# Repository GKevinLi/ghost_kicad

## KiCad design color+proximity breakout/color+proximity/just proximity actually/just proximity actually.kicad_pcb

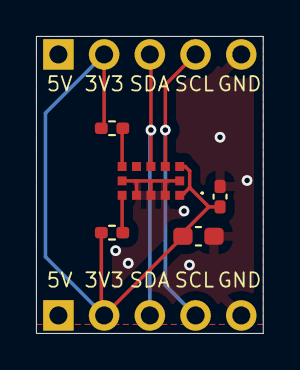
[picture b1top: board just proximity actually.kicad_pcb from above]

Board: 2 copper layers, 12.6 x 16.5 mm, 7 parts (0 on the bottom side), 7 nets.

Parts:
C11: 0.1u; C_0402_1005Metric_Pad0.74x0.62mm_HandSolder
C12: 4.7u; C_0603_1608Metric_Pad1.08x0.95mm_HandSolder
IC1: VL53L4CDV0DH_1; VL53L4CDV0DH1
J4, J4#2: Conn_01x05; PinHeader_1x05_P2.54mm_Vertical
R20, R21: 10k; R_0402_1005Metric_Pad0.72x0.64mm_HandSolder

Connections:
+3.3V: C11.1, C12.1, IC1.1 (AVDDVCSEL_1), IC1.11 (AVDD), IC1.13 (AVDDVCSEL_2), J4.2, J4#2.2, R20.2, R21.1
+5V: J4.1, J4#2.1
/scl: IC1.10 (SCL), J4.4, J4#2.4
/sda: IC1.9 (SDA), J4.3, J4#2.3
GND: C11.2, C12.2, IC1.2 (AVSSVCSEL), IC1.3 (GND), IC1.4 (GND2), IC1.6 (GND3), IC1.12 (GND4), J4.5, J4#2.5
unnamed: IC1.7 (GPIO1), R20.1
unnamed: IC1.5 (XSHUT), R21.2

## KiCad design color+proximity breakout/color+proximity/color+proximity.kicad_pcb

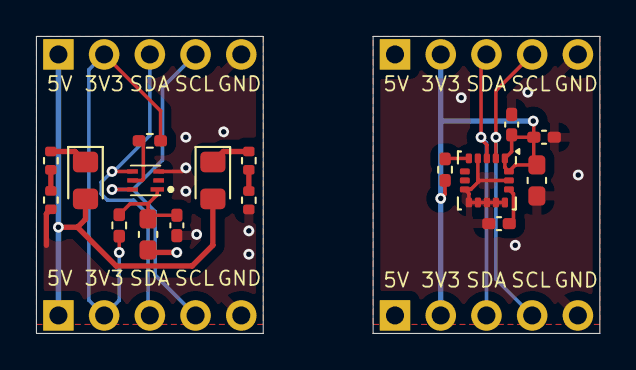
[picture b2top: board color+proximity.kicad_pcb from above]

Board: 2 copper layers, 31.3 x 16.5 mm, 21 parts (0 on the bottom side), 13 nets.

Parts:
C4: 1u; C_0603_1608Metric_Pad1.08x0.95mm_HandSolder
C5, C7, C10: 0.1u; C_0402_1005Metric_Pad0.74x0.62mm_HandSolder
C8: 2.2u; C_0603_1608Metric_Pad1.08x0.95mm_HandSolder
C9: 10n; C_0402_1005Metric_Pad0.74x0.62mm_HandSolder
D1, D2: WHITE; LED_0805_2012Metric_Pad1.15x1.40mm_HandSolder
IC2: ISL29125IROZ-T7; ISL29125IROZT7
J4, J4#2, J4#3, J4#4: Conn_01x05; PinHeader_1x05_P2.54mm_Vertical
R15: 100; R_0402_1005Metric_Pad0.72x0.64mm_HandSolder
R16, R19: 4.7k; R_0402_1005Metric_Pad0.72x0.64mm_HandSolder
R17, R18, R30, R32: 120; R_0402_1005Metric
U6: ICM-20602; LGA-16_3x3mm_P0.5mm_LayoutBorder3x5y

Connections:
+3.3V: C7.1, C8.1, C9.1, J4.2, J4#2.2, J4#3.2, J4#4.2, R15.2, R16.1, R19.1, U6.1 (VDDIO), U6.16 (VDD)
+5V: D1.2 (A), D2.2 (A), J4.1, J4#2.1, J4#3.1, J4#4.1
/scl: IC2.6 (SCL), J4.4, J4#2.4, J4#3.4, J4#4.4, U6.2 (SCL/SPC)
/sda: IC2.4 (SDA), J4.3, J4#2.3, J4#3.3, J4#4.3, U6.3 (SDA/SDI)
GND: C4.2, C5.2, C7.2, C8.2, C9.2, C10.2, IC2.3 (GND), J4.5, J4#2.5, J4#3.5, J4#4.5, R30.2, R32.2, U6.4 (SAO/SD0), U6.8 (FSYNC), U6.9 (GND), U6.10 (GND), U6.11 (GND), U6.12 (GND), U6.13 (GND), U6.15 (GND)
unnamed: D1.1 (K), R17.1
unnamed: D2.1 (K), R18.1
unnamed: C4.1, C5.1, IC2.1 (VDD), R15.1
unnamed: IC2.5 (~INT), R16.2
unnamed: R17.2, R30.1
unnamed: R18.2, R32.1
unnamed: C10.1, U6.14 (REGOUT)
unnamed: R19.2, U6.5 (~CS)

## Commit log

2025-11-09 step files and stuff (idk i might have fucked up the settings)
